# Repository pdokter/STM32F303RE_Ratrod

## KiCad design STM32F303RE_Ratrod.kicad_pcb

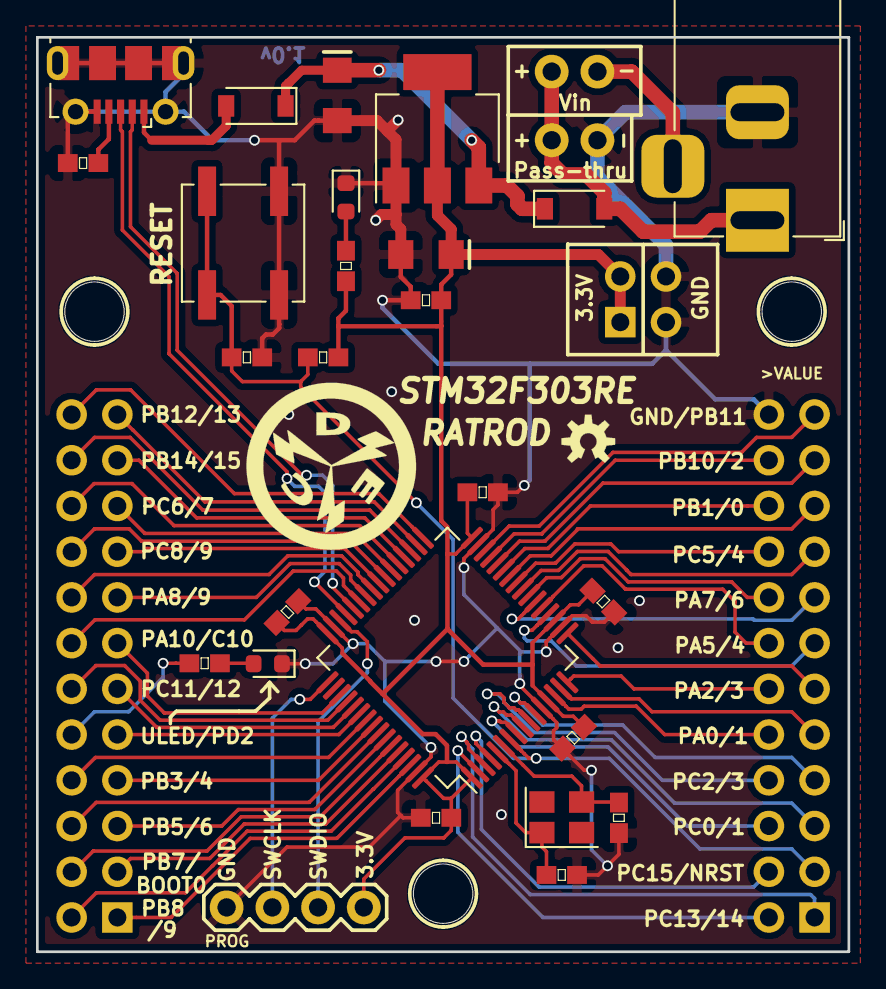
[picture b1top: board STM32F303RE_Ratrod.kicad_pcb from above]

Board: 2 copper layers, 45.1 x 50.8 mm, 34 parts (0 on the bottom side), 62 nets.

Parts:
>NAME: >VALUE; STAND-OFF
>NAME#2, >NAME#3: >VALUE; STAND-OFF
C1, C2: 10uF; EIA3216_2
C3, C4, C7, C8, C9, C10: 0.1uF; 0603
C5, C6: 18pF; 0603
C11: 2.2uF; 0603
D1, D2: D_Schottky; D_SOD-123
D3, D4: RED; D_0603_1608Metric
J1: USB_B_Micro; USB_Micro-B_Molex-105017-0001
J2: CONN_01X02; 1X02_NO_SILK
J3: Barrel_Jack_Switch; BarrelJack_Horizontal
J4: PROG; 1X04
J5: Power Pass-thru; 1X02_NO_SILK
J6, J7: CONN_02X12; PinHeader_2x12_P2.54mm_Vertical_NS
J8: CONN_02X02; PinHeader_2x02_P2.54mm_Vertical_NS
R1: 100k; 0603
R2, R4: 220; 0603
R3: 10k; 0603
S1: Tact_Sw; SW_SPST_B3SL-1022P
U1: AZ1117-3.3; SOT-223-3_TabPin2
U2: STM32F303RETx; LQFP-64_10x10mm_P0.5mm
Y1: Crystal_32MHz; Crystal_SMD_3225-4Pin_3.2x2.5mm

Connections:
3.3V: C2.1, C3.1, C7.1, C8.1, C9.1, C10.1, C11.1, J4.1, J8.1, J8.2, R2.1, R3.1, U1.2, U2.1, U2.13, U2.19, U2.32, U2.48, U2.64
BOOT0: J7.3, U2.60
GND: C1.2, C2.2, C3.2, C4.2, C5.2, C6.2, C7.2, C8.2, C9.2, C10.2, C11.2, D3.1, D4.1, J1.5, J1.6, J3.2, J4.4, J5.2, J6.24, J8.3, J8.4, R1.2, S1.1, S1.4, U1.1, U2.12, U2.18, U2.31, U2.47, U2.63
NRST: C4.1, J6.3, R3.2, S1.2, S1.3, U2.7
unnamed: C1.1, D1.1, D2.1, U1.3
unnamed: C5.1, U2.5, Y1.1
unnamed: C6.1, U2.6, Y1.3
unnamed: D1.2, J1.1
unnamed: D3.2, R2.2
unnamed: D4.2, R4.2
unnamed: J1.4, R1.1
unnamed: J2.1, J3.3
PA0: J6.10, U2.14
PA1: J6.9, U2.15
PA2: J6.12, U2.16
PA3: J6.11, U2.17
PA4: J6.13, U2.20
PA5: J6.14, U2.21
PA6: J6.15, U2.22
PA7: J6.16, U2.23
PA8: J7.16, U2.41
PA9: J7.15, U2.42
PA10: J7.14, U2.43
PB0: J6.19, U2.26
PB1: J6.20, U2.27
PB2: J6.21, U2.28
PB3: J7.8, U2.55
PB4: J7.7, U2.56
PB5: J7.6, U2.57
PB6: J7.5, U2.58
PB7: J7.4, U2.59
PB8: J7.2, U2.61
PB9: J7.1, U2.62
PB10: J6.22, U2.29
PB11: J6.23, U2.30
PB12: J7.24, U2.33
PB13: J7.23, U2.34
PB14: J7.22, U2.35
PB15: J7.21, U2.36
PC0: J6.6, U2.8
PC1: J6.5, U2.9
PC2: J6.8, U2.10
PC3: J6.7, U2.11
PC4: J6.17, U2.24
PC5: J6.18, U2.25
PC6: J7.20, U2.37
PC7: J7.19, U2.38
PC8: J7.18, U2.39
PC9: J7.17, U2.40
PC10: J7.13, U2.51
PC11: J7.12, U2.52
PC12: J7.11, U2.53
PC13: J6.2, U2.2
PC14: J6.1, U2.3
PC15: J6.4, U2.4
PD2: J7.9, U2.54
SWCLK: J4.3, U2.49
SWDIO: J4.2, U2.46
USB_D+: J1.3, U2.45
USB_D-: J1.2, U2.44
U_LED: J7.10, R4.1
Vin: D2.2, J2.2, J3.1, J5.1

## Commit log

2019-01-29 First commit, version 0.1
2019-01-30 Moved a couple caps, put labels on the bottom, fixed logos.
2019-01-30 Tweaks to logo for protos.
